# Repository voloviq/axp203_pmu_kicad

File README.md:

# axp203_pmu_kicad
AXP203 Power Supply Project draw in KiCad which can be use in any other project as an component

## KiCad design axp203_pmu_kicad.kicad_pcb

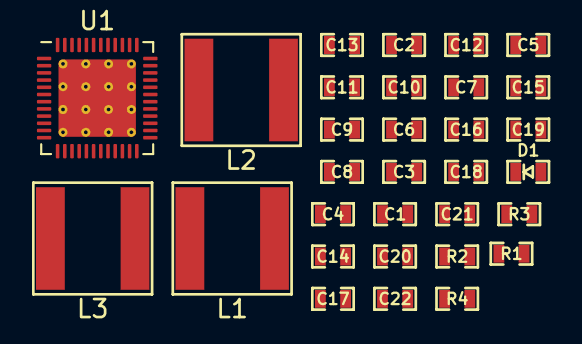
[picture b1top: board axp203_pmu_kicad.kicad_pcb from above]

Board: 2 copper layers, 31 parts (0 on the bottom side), 21 nets, no tracks yet.

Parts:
C1, C2, C4, C5, C6, C7, C8, C13, C14, C15, C16, C17, C18, C19, C20, C22: 10uF/10V; 10uF_10V_0603
C3: 1uF/10V; 1uF_0603
C9, C10, C11, C12: 4.7uF/10V; 4_7uF_0603
C21: 100nF/50V; 100nF_0603
D1: Green; LED_KPT-1608CGCK
L1, L2, L3: 4.7uH; IHLP2020BZER4R7M01
R1: 0.033R; 0R033_0603
R2: 100R/63mW; 100R_0603
R3, R4: 1k; 1k_0603
U1: AXP203; AXP203_QFN48

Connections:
/AXP203 PMU/DCDC2_VOUT: C14.1, L3.2, U1.10
/AXP203 PMU/DCDC3_VOUT: C13.1, C15.2, C16.2, L2.2, U1.13, U1.17, U1.40
/AXP203 PMU/DCIN: C4.1, U1.32, U1.33
/AXP203 PMU/IPS_VOUT: C17.1, C18.1, C19.1, C20.1, C21.1, C22.1, R4.1, U1.7, U1.14, U1.21, U1.29, U1.34, U1.35, U1.44
/AXP203 PMU/LDO1_VOUT: C9.2, U1.28
/AXP203 PMU/LDO2_VOUT: C10.2, U1.12
/AXP203 PMU/LDO3_VOUT: C12.2, U1.41
/AXP203 PMU/LDO4_VOUT: C11.2, U1.11
/AXP203 PMU/VBAT: C1.1, C3.2, C7.1, R1.2, U1.38, U1.39, U1.42, U1.43
/AXP203 PMU/VBUS: C5.1, U1.31
GND: C1.2, C2.2, C4.2, C5.2, C6.2, C7.2, C8.2, C9.1, C10.1, C11.1, C12.1, C13.2, C14.2, C15.1, C16.1, C17.2, C18.2, C19.2, C20.2, C21.2, C22.2, R2.2, R3.2, U1.9, U1.16, U1.22, U1.46, U1.49
unnamed: C2.1, U1.26
unnamed: C3.1, C8.1, L1.1, R1.1
unnamed: C6.1, U1.24
unnamed: D1.1, R4.2
unnamed: D1.2, U1.36
unnamed: L1.2, U1.45
unnamed: L2.1, U1.15
unnamed: L3.1, U1.8
unnamed: R2.1, U1.37
unnamed: R3.1, U1.23

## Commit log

2019-12-24 Initial
2019-12-24 Updated PCB
2020-04-08 Continue activity
2020-05-13 Schematic finished, pcb components added in pcb, axp schematic checked
2020-05-14 Updated schematic - corp name
